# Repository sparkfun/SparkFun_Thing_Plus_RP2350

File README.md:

SparkFun Thing Plus - RP2350
========================================

[*SparkFun Thing Plus - RP2350 (WRL-25134)*](https://www.sparkfun.com/products/25134)

The SparkFun Thing Plus - RP2350 is a dynamic and powerful wireless development platform in the Thing Plus form factor. Built around the RP2350 microcontroller from the Raspberry Pi Foundation, this board includes their radio module for single-band 2.4 GHz WiFi 4 (802.11n) and Bluetooth<sup>&reg;</sup> 5.2 along with standard hardware components found on all Thing Plus Boards. This includes on-board Lithium Ion (LiPo) battery charging and fuel gauge circuits, &micro;SD card socket, Qwiic connector, and the Thing Plus pinout, allowing use of the RP2350 Thing Plus in a wide variety of both local and remote applications.

The RP2350 Thing Plus includes two expanded memory options: 16MB of external Flash and 8MB PSRAM connected to the RP2350's QSPI controller. This Thing Plus board works with C/C++ using the Pico SDK, MicroPython, CircuitPython, and Arduino development environments.

Repository Contents
-------------------

* **/Documents** - Data sheets, additional product information 
* **/Examples** - Example code 
* **/Hardware** - Eagle design files (.brd, .sch)
* **/Production** - Production panel files (.brd)
* **/docs** - GitHub Pages documentation files

Documentation
--------------
* **[Hookup Guide](https://docs.sparkfun.com/SparkFun_Thing_Plus_RP2350/introduction/)** - Basic hookup guide for the Thing Plus - RP2350.
* [PSRAM Library and Examples](https://github.com/sparkfun/sparkfun-pico) - A cmake library and examples to use the on-board PSRAM when developing in the Raspberry Pi [pico-sdk](https://github.com/raspberrypi/pico-sdk).

Product Versions
----------------
* [WRL-25134](https://www.sparkfun.com/products/25134) - SparkFun Thing Plus - RP2350 development board.

License Information
-------------------

This product is _**open source**_! 

Please review the LICENSE.md file for license information. 

If you have any questions or concerns on licensing, please contact technical support on our [SparkFun forums](https://forum.sparkfun.com/viewforum.php?f=152).

Distributed as-is; no warranty is given.

- Your friends at SparkFun.

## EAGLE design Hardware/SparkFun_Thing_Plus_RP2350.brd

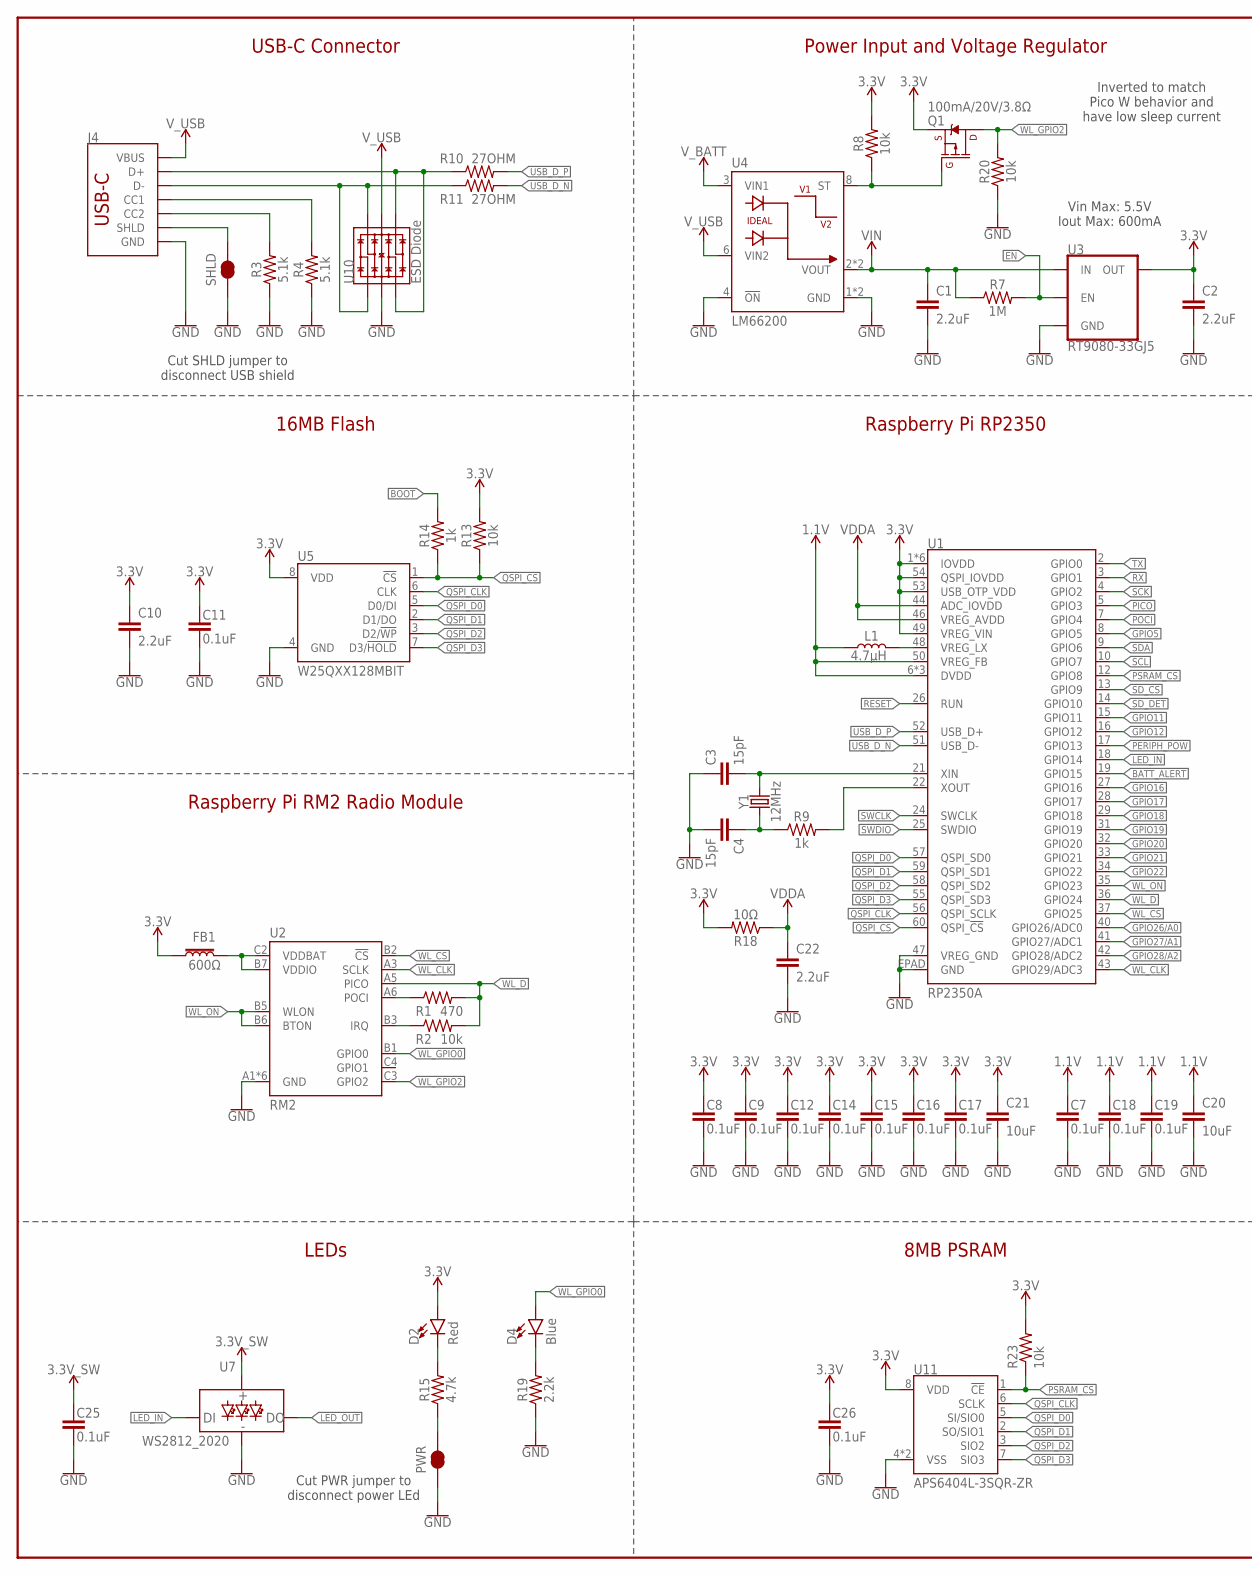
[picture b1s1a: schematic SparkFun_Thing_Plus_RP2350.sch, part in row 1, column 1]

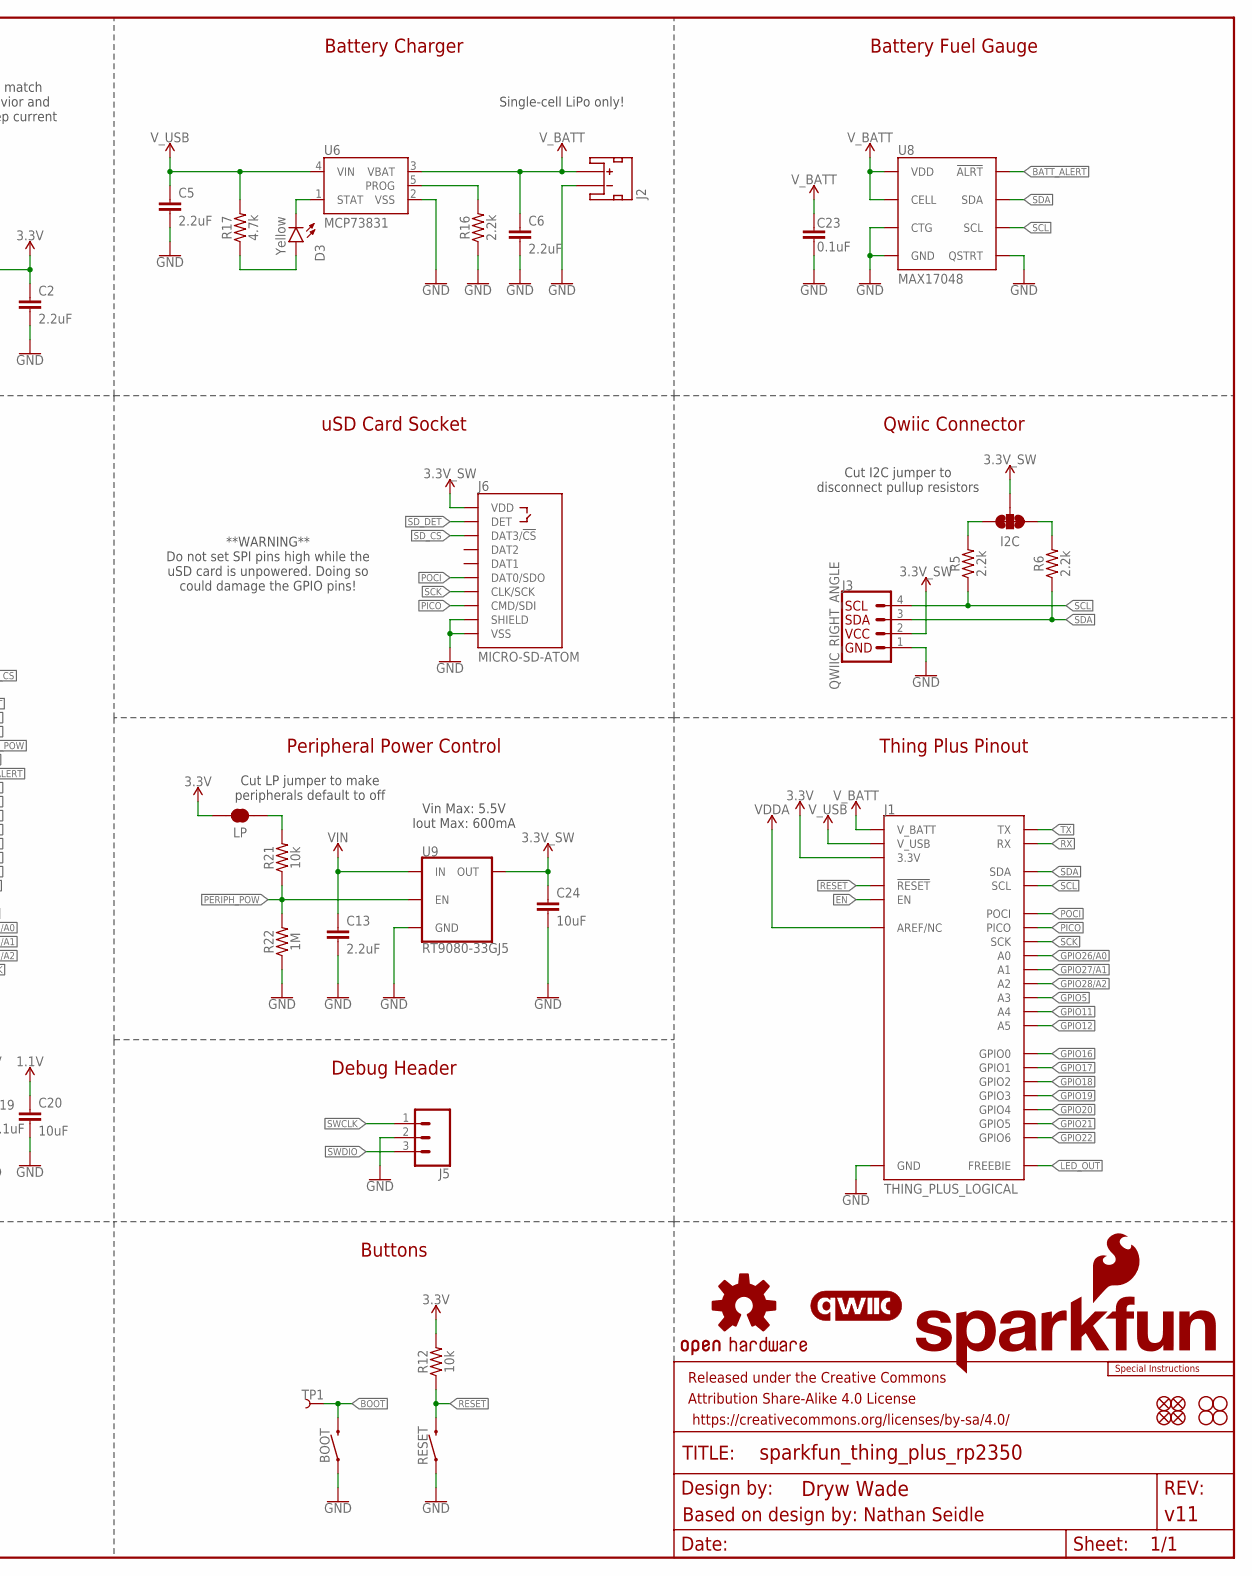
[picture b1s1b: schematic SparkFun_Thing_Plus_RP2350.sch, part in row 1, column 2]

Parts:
BOOT: MOMENTARY-SWITCH-SPST-SMD-4.6X2.8MM; TACTILE_SWITCH_SMD_4.6X2.8MM
C1, C2, C5, C6, C10, C13, C22: 2.2uF; 0402-TIGHT
C3, C4: 15pF; 0402-TIGHT
C7, C8, C9, C11, C12, C14, C15, C16, C17, C18, C19, C23, C25, C26: 0.1uF; 0402-TIGHT
C20, C21, C24: 10uF; 0402-TIGHT
D2: Red; LED-0603
D3: Yellow; LED-0603
D4: Blue; LED-0603
FB1: 600Ω; 0805
FD1, FD2, FD3, FD4: FIDUCIALUFIDUCIAL; FIDUCIAL-MICRO
FRAME1: FRAME-LEDGER; CREATIVE_COMMONS
H1, H2, H3, H4: STAND-OFF
I2C: JUMPER-SMT_3_2-NC_TRACE_SILK; SMT-JUMPER_3_2-NC_TRACE_SILK
J1: THING_PLUS_LOGICAL; THING_PLUS
J2: JST_2MM_MALE; JST-2-SMD
J3: QWIIC_RIGHT_ANGLE; JST04_1MM_RA
J4: USB_C_4-LAYER_PADS; USB-C-16P_4LAYER-PADS
J5: CONN_031X03_NO_SILK; 1X03_NO_SILK
J6: MICRO-SD-ATOM; MICROSD_ATOM
L1: 4.7μH; 1008(2520)
LOGO1: SFE_LOGO_NAME_FLAME.1_INCH; SFE_LOGO_NAME_FLAME_.1
LOGO2: OSHW-LOGOS; OSHW-LOGO-S
LOGO3: QWIIC_LOGO_4MM; QWIIC_4MM
LOGO5: SPECIAL_INSTRUCTIONS-ORDERING; ORDERING_INSTRUCTIONS
LP: JUMPER-SMT_2_NC_TRACE_SILK; SMT-JUMPER_2_NC_TRACE_SILK
PWR: JUMPER-SMT_2_NC_TRACE_SILK; SMT-JUMPER_2_NC_TRACE_SILK
Q1: 100mA/20V/3.8Ω; SOT-416FL
R1: 470; 0402-TIGHT
R2, R8, R12, R13, R20, R21, R23: 10k; 0402-TIGHT
R3, R4: 5.1k; 0402-TIGHT
R5, R6, R16, R19: 2.2k; 0402-TIGHT
R7, R22: 1M; 0402-TIGHT
R9, R14: 1k; 0402-TIGHT
R10, R11: 27OHM; 0402-TIGHT
R15, R17: 4.7k; 0402-TIGHT
R18: 10Ω; 0402-TIGHT
RESET: MOMENTARY-SWITCH-SPST-SMD-4.6X2.8MM; TACTILE_SWITCH_SMD_4.6X2.8MM
SHLD: JUMPER-SMT_2_NC_TRACE_SILK; SMT-JUMPER_2_NC_TRACE_SILK
TP1: TEST-POINT3X5; PAD.03X.05
U1: RP2350A
U2: RM2
U3, U9: RT9080-33GJ5; SOT23-5
U4: LM66200; SOT8
U5: W25QXX128MBIT; WSON-8-6X5-SKINNY_CENTERPAD
U6: MCP73831; SOT23-5
U7: WS2812_2020; WS2812-2020
U8: MAX17048; DFN-8
U10: ESD Diode; SOT-23-6
U11: APS6404L-3SQR-ZR
Y1: 12MHz; CRYSTAL-SMD-2X2.5MM

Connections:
1.1V: C7.1, C18.1, C19.1, C20.1, L1.1, U1.6 (DVDD), U1.23 (DVDD), U1.39 (DVDD), U1.50 (VREG_FB)
3.3V: C2.1, C8.1, C9.1, C10.1, C11.1, C12.1, C14.1, C15.1, C16.1, C17.1, C21.1, C26.1, D2.A, FB1.1, J1.27 (3.3V), LP.2, Q1.2 (S), R8.2, R12.2, R13.2, R18.2, R23.2, U1.1 (IOVDD), U1.11 (IOVDD), U1.20 (IOVDD), U1.30 (IOVDD), U1.38 (IOVDD), U1.45 (IOVDD), U1.49 (VREG_VIN), U1.53 (USB_OTP_VDD), U1.54 (QSPI_IOVDD), U3.5 (OUT), U5.8 (VDD), U11.8 (VDD)
3.3V_SW: C24.1, C25.1, I2C.2, J3.2, J6.4 (VDD), U7.VCC, U9.5 (OUT)
!BATT_ALERT!: U1.19 (GPIO15), U8.5 (!ALRT)
!BOOT!: BOOT.3 (2), BOOT.4 (2), R14.2, TP1.1
!RESET!: J1.28 (!RESET), R12.1, RESET.3 (2), RESET.4 (2), U1.26 (RUN)
BAT_SW: Q1.1 (G), R8.1, U4.8 (ST)
EN: J1.11 (EN), R7.2, U3.3 (EN)
GND: BOOT.1, BOOT.2 (1), C1.2, C2.2, C3.1, C4.2, C5.2, C6.2, C7.2, C8.2, C9.2, C10.2, C11.2, C12.2, C13.2, C14.2, C15.2, C16.2, C17.2, C18.2, C19.2, C20.2, C21.2, C22.2, C23.2, C24.2, C25.2, C26.2, J1.25 (GND), J2.1 (-), J3.1, J4.GND, J4.GND2 (GND), J5.2, J6.6 (VSS), J6.SHIELD1 (SHIELD), J6.SHIELD2 (SHIELD), J6.SHIELD3 (SHIELD), J6.SHIELD4 (SHIELD), PWR.1, R3.1, R4.1, R16.1, R19.1, R20.1, R22.1, RESET.1, RESET.2 (1), SHLD.1, U1.47 (VREG_GND), U1.EPAD (GND), U2.A1 (GND), U2.A4 (GND), U2.A7 (GND), U2.B4 (GND), U2.C1 (GND), U2.C7 (GND), U3.2 (GND), U4.1 (GND), U4.4 (!ON!), U4.5 (GND), U5.4 (GND), U6.2 (VSS), U7.GND, U8.1 (CTG), U8.4 (GND), U8.6 (QSTRT), U8.9 (GND), U9.2 (GND), U10.2 (VSS), U11.4 (VSS), U11.9 (VSS)
GPIO5: J1.21 (A3), U1.8 (GPIO5)
GPIO11: J1.20 (A4), U1.15 (GPIO11)
GPIO12: J1.19 (A5), U1.16 (GPIO12)
GPIO16: J1.9 (GPIO0), U1.27 (GPIO16)
GPIO17: J1.8 (GPIO1), U1.28 (GPIO17)
GPIO18: J1.7 (GPIO2), U1.29 (GPIO18)
GPIO19: J1.6 (GPIO3), U1.31 (GPIO19)
GPIO20: J1.5 (GPIO4), U1.32 (GPIO20)
GPIO21: J1.4 (GPIO5), U1.33 (GPIO21)
GPIO22: J1.3 (GPIO6), U1.34 (GPIO22)
GPIO26/A0: J1.24 (A0), U1.40 (GPIO26/ADC0)
GPIO27/A1: J1.23 (A1), U1.41 (GPIO27/ADC1)
GPIO28/A2: J1.22 (A2), U1.42 (GPIO28/ADC2)
LED_IN: U1.18 (GPIO14), U7.DI
LED_OUT: J1.13 (FREEBIE), U7.DO
unnamed: FB1.2, U2.B7 (VDDIO), U2.C2 (VDDBAT)
unnamed: R1.1, U2.A6 (POCI)
unnamed: R2.1, U2.B3 (IRQ)
unnamed: D4.C, R19.2
unnamed: J4.B5 (CC2), R3.2
unnamed: J4.A5 (CC1), R4.2
unnamed: J4.A7 (D-), J4.B7 (D-), R11.1, U10.1 (IO1), U10.6 (IO4)
unnamed: J4.A6 (D+), J4.B6 (D+), R10.1, U10.3 (IO2), U10.4 (IO3)
unnamed: I2C.3, R5.2
unnamed: I2C.1, R6.2
unnamed: LP.1, R21.2
unnamed: C3.2, U1.21 (XIN), Y1.P3 (2)
unnamed: C4.1, R9.1, Y1.P1 (1)
unnamed: R9.2, U1.22 (XOUT)
unnamed: D2.C, R15.2
unnamed: PWR.2, R15.1
unnamed: R16.2, U6.5 (PROG)
unnamed: D3.A, R17.1
unnamed: D3.C, U6.1 (STAT)
unnamed: L1.2, U1.48 (VREG_LX)
PERIPH_POW: R21.1, R22.2, U1.17 (GPIO13), U9.3 (EN)
PICO: J1.17 (PICO), J6.3 (CMD/SDI), U1.5 (GPIO3)
POCI: J1.16 (POCI), J6.7 (DAT0/SDO), U1.7 (GPIO4)
PSRAM_!CS!: R23.1, U1.12 (GPIO8), U11.1 (!CE!)
QSPI_!CS!: R13.1, R14.1, U1.60 (QSPI_!CS!), U5.1 (!CS!)
QSPI_CLK: U1.56 (QSPI_SCLK), U5.6 (CLK), U11.6 (SCLK)
QSPI_D0: U1.57 (QSPI_SD0), U5.5 (D0/DI), U11.5 (SI/SIO0)
QSPI_D1: U1.59 (QSPI_SD1), U5.2 (D1/DO), U11.2 (SO/SIO1)
QSPI_D2: U1.58 (QSPI_SD2), U5.3 (D2/!WP!), U11.3 (SIO2)
QSPI_D3: U1.55 (QSPI_SD3), U5.7 (D3/!HOLD!), U11.7 (SIO3)
RX: J1.15 (RX), U1.3 (GPIO1)
SCK: J1.18 (SCK), J6.5 (CLK/SCK), U1.4 (GPIO2)
SCL: J1.2 (SCL), J3.4, R5.1, U1.10 (GPIO7), U8.7 (SCL)
SDA: J1.1 (SDA), J3.3, R6.1, U1.9 (GPIO6), U8.8 (SDA)
SD_!CS!: J6.2 (DAT3/!CS!), U1.13 (GPIO9)
SD_DET: J6.9 (DET), U1.14 (GPIO10)
SHLD: J4.SHLD1 (SHLD), J4.SHLD2 (SHLD), J4.SHLD3 (SHLD), J4.SHLD4 (SHLD), SHLD.2
SWCLK: J5.1, U1.24 (SWCLK)
SWDIO: J5.3, U1.25 (SWDIO)
TX: J1.14 (TX), U1.2 (GPIO0)
USB_D_N: R11.2, U1.51 (USB_D-)
USB_D_P: R10.2, U1.52 (USB_D+)
VDDA: C22.1, J1.26 (AREF/NC), R18.1, U1.44 (ADC_IOVDD), U1.46 (VREG_AVDD)
VIN: C1.1, C13.1, R7.1, U3.1 (IN), U4.2 (VOUT), U4.7 (VOUT), U9.1 (IN)
V_BATT: C6.1, C23.1, J1.12 (V_BATT), J2.2 (+), U4.3 (VIN1), U6.3 (VBAT), U8.2 (CELL), U8.3 (VDD)
V_USB: C5.1, J1.10 (V_USB), J4.VBUS1 (VBUS), J4.VBUS2 (VBUS), R17.2, U4.6 (VIN2), U6.4 (VIN), U10.5 (VCC)
WL_CLK: U1.43 (GPIO29/ADC3), U2.A3 (SCLK)
WL_CS: U1.37 (GPIO25), U2.B2 (!CS!)
WL_D: R1.2, R2.2, U1.36 (GPIO24), U2.A5 (PICO)
WL_GPIO0: D4.A, U2.B1 (GPIO0)
WL_GPIO2: Q1.3 (D), R20.2, U2.C3 (GPIO2)
WL_ON: U1.35 (GPIO23), U2.B5 (WLON), U2.B6 (BTON)

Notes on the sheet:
USB-C Connector
Power Input and Voltage Regulator
Battery Charger
Battery Fuel Gauge
Qwiic Connector
uSD Card Socket
Thing Plus Pinout
Peripheral Power Control
Debug Header
Raspberry Pi RP2350
16MB Flash
Raspberry Pi RM2 Radio Module
LEDs
Cut SHLD jumper to disconnect USB shield
Inverted to match Pico W behavior and have low sleep current
Cut I2C jumper to disconnect pullup resistors
Cut PWR jumper to disconnect power LEd
Buttons
Cut LP jumper to make peripherals default to off
Vin Max: 5.5V Iout Max: 600mA
Single-cell LiPo only!
8MB PSRAM
**WARNING** Do not set SPI pins high while the uSD card is unpowered. Doing so could damage the GPIO pins!
Based on design by: Nathan Seidle

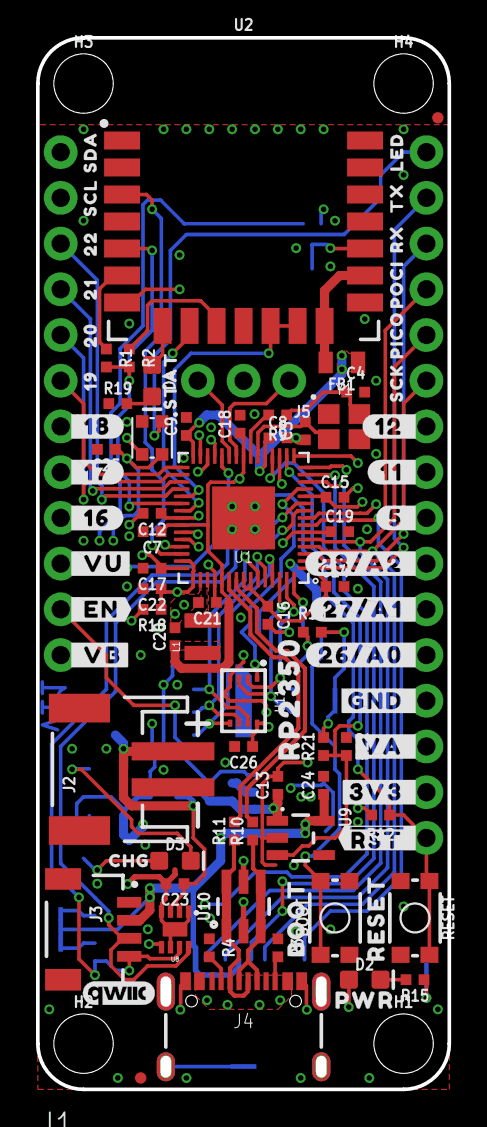
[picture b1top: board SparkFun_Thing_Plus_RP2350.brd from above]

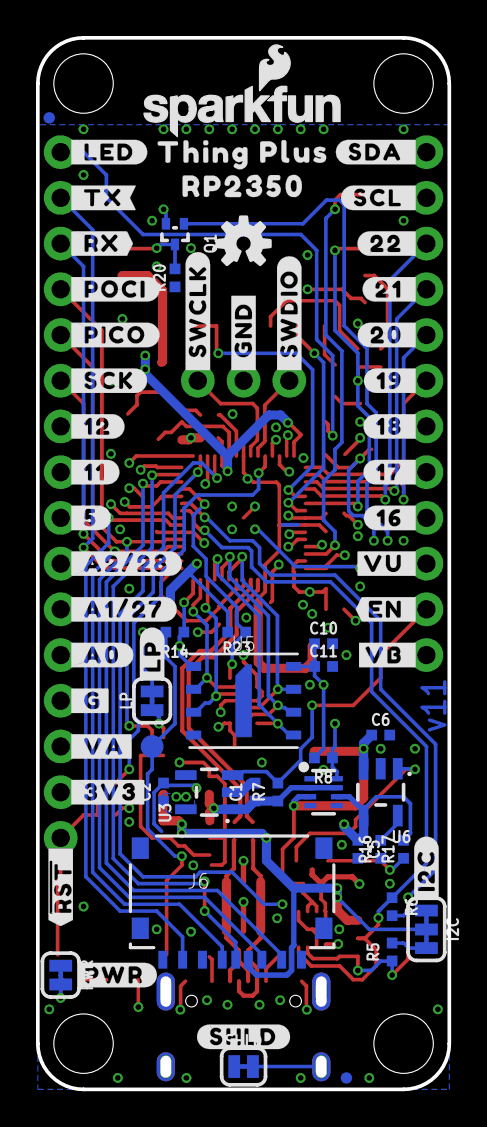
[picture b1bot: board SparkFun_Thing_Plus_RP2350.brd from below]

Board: 4 copper layers, 22.9 x 58.4 mm, 164 parts (67 on the bottom side), 76 nets.

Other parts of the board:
U$1: SDA0
U$2: SCL0
U$3: TX0
U$4: RX0
U$5: PICO0
U$6: POCI0
U$7: SCK0
U$8: #SDA_#0
U$9: #SCL_#0
U$10: #_TX#0
U$11: #_RX#0
U$12: #_POCI#0
U$13: #_PICO#0
U$14: #_SCK#0
U$15: #_GND#0
U$16: #_A0#0
U$17: #_3V3#0
U$18, U$61: ##RST#_#0
U$19: #I2C#0
U$20: #_SWCLK#0
U$21: #_SWDIO#0
U$22: #_VB#0
U$23: #_VU#0
U$24: #_EN#0
U$25: #3V3_#0
U$26: #LP#0
U$27: #GND_#0
U$28: #11_#0
U$29: #26#A0_#0
U$30: #27#A1_#0
U$31: #28#A2_#0
U$32: BOOT0
U$33: RESET0
U$34: #VU_#0
U$35: #VB_#0
U$36: #EN_#0
U$38: #_A1#27#0
U$39: #_A2#28#0
U$40: #PWR#0
U$41: #SHLD#0
U$42: THING_PLUS0
U$43, U$45: RP23500
U$44: #_G#0
U$46: #_16#0
U$47: #_17#0
U$48: #_18#0
U$49: CHG0
U$50: 200
U$51: 210
U$52: 220
U$53: #22_#0
U$54: #21_#0
U$55: #20_#0
U$56: #19_#0
U$57: #18_#0
U$58: #17_#0
U$59: #16_#0
U$60: 190
U$62: PWR0
U$63: STAT0
U$64: #5_#0
U$65: #12_#0
U$66: #_12#0
U$67: LED0
U$68: #_LED#0
U$69: #_5#0
U$70: #_11#0
U$72: #VA_#0
U$73: #_VA#0

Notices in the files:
parts and their libraries:
SparkFun-Aesthetics: Licensing: Creative Commons ShareAlike 4.0 International - https://creativecommons.org/licenses/by-sa/4.0
SparkFun-Aesthetics: Released under the Creative Commons Attribution Share-Alike 4.0 License
SparkFun-Aesthetics: https://creativecommons.org/licenses/by-sa/4.0
